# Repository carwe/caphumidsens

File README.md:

ARCHIVED on github -> migrated to codeberg: https://codeberg.org/carwe/caphumidsens

<b>code not usable due to never debugged bugs</b>

<b>code not usable due to never debugged bugs</b>

<b>code not usable due to never debugged bugs</b>

<b>code not usable due to never debugged bugs</b>

caphumidsens
============
Contains EAGLE-files for a pcb to convert soil moisture into frequency.

There are various revisions of the board:

classic design with NE555
-------------------------

###caphumidsens rev1
This was more or less a test, if the idea is working. It is quite big and unoptimized. Also the design of the capacitator is unnecessary complex.<br>
You need one NE555 (or CMOS-equivalent like TLC555) in SO-8, the other parts are of size 0805. C1=10nF; C2=100nF; R1=R2=120kOhm; D1=1N4148<br>
The chosen values let the output oscillate with around 74kHz, when dry and in air, down to around 4kHz, when the cap-part of the board is put into pure water, if you have chosen the TTL-555.

###caphumidsens rev2
...died an early death and was never physically fabricated.

###caphumidsens rev3
...is space-optimized and the components are nicely placed in a row, the draw-back is, they are too close - unfortuntely I had some of them fabricated, so it needed some fiddling to solder. <b>Do not use this layout.</b> In the discussion about this board some ideas came along: you probably want to measure the humidity in the middle of the soil, at least not directly on the surface, where it varies most. And there should be some kind of safety-margin, you don't want to change the capacitance by moving it slightly in and out of the soil. Next design should adress this.

###caphumidsens rev4
Here the capacitator was moved, so the humidity on the surface is no longer significant. Also the parts, which were too close to each other, got more space between them.

<pre>Measurements (frequency in kHz):
                Rev1/TTL        Rev1/CMOS        Rev3/CMOS        Rev4/CMOS
air              74,9              66,8            91,6              ?
dry soil         73,1              65,3            91,3              ?
half-wet soil    64,0              52,5            73,4              ?
wet soil         13,4              17,8            37,6              ?
water             3,4               ?               ?                ?</pre>

redesign with ATtiny
--------------------

###caphumidsens rev5
Lately I discussed about the project, and it quickly became clear, that it should be possible to connect output-pins of more than one caphumidsens-pcb over a single line with a master-controller. Using a bus has clear advantages (otherwise, you have to use a dedicated line to transport each signal, of course), so I designed a first draft.

With a ATtiny25/45/85 (maybe ATtiny13A too, if the code fits into it - comparator is existent there too, and the pinout is the same) I tried to create a NE555-similar structure. A capacitator is charged to a higher voltage, then discharged to a lower voltage, and a comparator toggles the (dis-)charging.

You have to decide if you want to use the internal voltage reference or not. If yes, you have to sense the voltage with AIN1 and compare it to the internal voltage reference and AIN0 as external voltage reference. If no, you have to sense the voltage with AIN0 and compare it witho two external voltage references on ADC0-ADC3. Some time ago I wrote here you could not compare against the internal reference and the multiplexer at the same time and save a pin - which is true, but you don't need to, it just requires another layout. To use the internal voltage reference for one side of the comparison, you have to have your sense pin as negative side on AIN1, and select the internal reference for the positive side of the AC. Then compare negative side AIN1 with AIN0 as the positive side of the AC. But, this is not what I designed.

I chose to use two external voltage references, created by division of VCC, same as in 555. This way it makes no difference what exact voltage VCC is, it can even change, the resulting frequency is independent. So you sense the voltage on AIN0 as positive side of the AC, and the multiplexer as negative side, and switch the input of the multiplexer as you charge (ADC1) and discharge (ADC2).

Pin 6 is set to VCC or GND to charge or discharge the capacitator, pin 5 senses the voltage and compares it to pin 3 or 7. On pin 1 (and maybe pin 2, if clock-ínput is not needed) you can talk a protocol you like - a simple frequency like the NE555 or something more complex, maybe pulling the line low against a central pull-resistor (I2C-like), sending your ID (stored in EEPROM) followed by the measured capacity. After you have written out a bit of your ID, you read it back, if another sensor is sending too (pulling the line dominates leaving the line alone, so the ID with the most "pulling bits" is the highest, CAN-like). The frequency of the messages is low enough, so that collisions should hardly occur, and if, you simply repeat your message.

Pin 1 is the reset/debugwire-pin too, so you can use debugwire to program the harder part of measuring the capacity, as you don't need the output-pin during this time. I have added small capacitators to even out the reference voltages, if that is necessary.

In the next days, I should receive some of them from the manufacturer.

Update five years later, 2017: yes I got them. and then I forgot them. And, I would not use Eagle anymore. Never again. Took me an hour to find an old version I could use with my licence, it brought me to tears what happened to this program after being bought by Autodesk. Everybody warned me to use this nonfree software, and I thought "whatever... works for me." - then reality hit.

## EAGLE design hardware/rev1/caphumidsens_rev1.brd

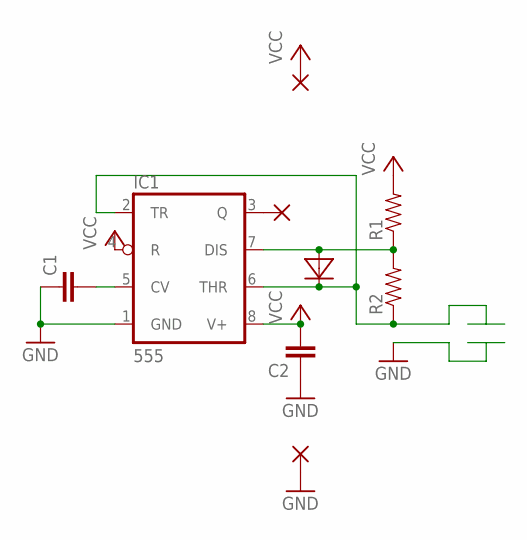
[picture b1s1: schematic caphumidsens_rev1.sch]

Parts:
C1, C2: CAP0805; 0805
D1: DIODE_0805
GND: WIREPADSMD2,54-5,08; SMD2,54-5,08
IC1: 555; SO08
OUT: WIREPADSMD2,54-5,08; SMD2,54-5,08
R1, R2: RESISTOR0805-RES; 0805
VCC: WIREPADSMD2,54-5,08; SMD2,54-5,08

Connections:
CAP+: D1.1 (C), IC1.2 (TR), IC1.6 (THR), R2.1
GND: C1.1, C2.1, GND.1, IC1.1 (GND)
unnamed: D1.2 (A), IC1.7 (DIS), R1.1, R2.2
unnamed: C1.2, IC1.5 (CV)
unnamed: IC1.3 (Q), OUT.1
VCC: C2.2, IC1.4 (R), IC1.8 (V+), R1.2, VCC.1

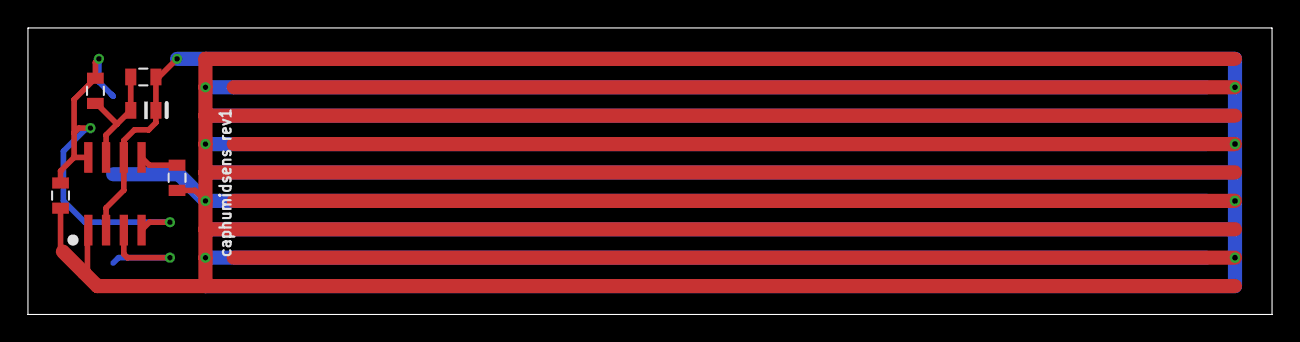
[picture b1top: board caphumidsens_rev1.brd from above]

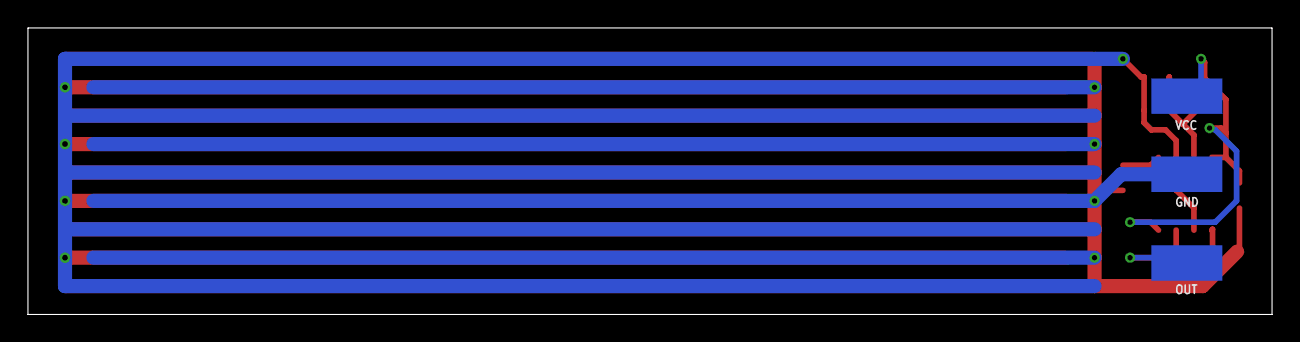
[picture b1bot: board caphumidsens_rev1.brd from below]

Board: 2 copper layers, 89.0 x 20.5 mm, 9 parts (3 on the bottom side), 6 nets.

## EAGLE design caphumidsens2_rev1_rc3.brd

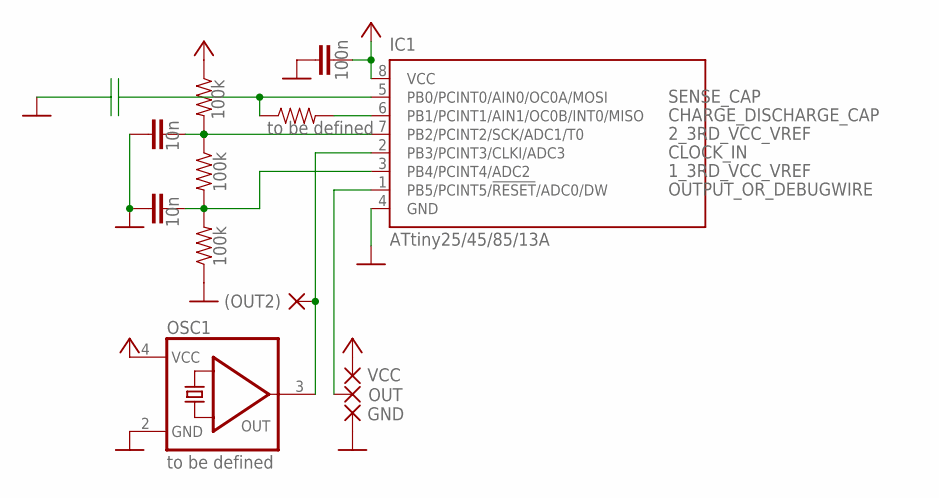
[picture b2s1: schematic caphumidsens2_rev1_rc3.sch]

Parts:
(OUT2): WIREPADSMD2,54-5,08; SMD1,27-2,54
C1: 100n; 0805
C2, C3: 10n; 0805
GND: WIREPADSMD2,54-5,08; SMD1,27-2,54
IC1: ATtiny25/45/85/13A; 8S1
OSC1: to be defined; XO32
OUT: WIREPADSMD2,54-5,08; SMD1,27-2,54
R1, R2, R3: 100k; 0805
R4: to be defined; 0805
VCC: WIREPADSMD2,54-5,08; SMD1,27-2,54

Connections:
1_3RD_VCC_VREF: C2.1, IC1.3 (PB4/PCINT4/ADC2), R2.2, R3.2
2_3RD_VCC_VREF: C3.2, IC1.7 (PB2/PCINT2/SCK/ADC1/T0), R1.2, R2.1
CHARGE_DISCHARGE_CAP: IC1.6 (PB1/PCINT1/AIN1/OC0B/INT0/MISO), R4.2
CLOCK_IN: (OUT2).1, IC1.2 (PB3/PCINT3/CLKI/ADC3), OSC1.3 (OUT)
GND: C1.1, C2.2, C3.1, GND.1, IC1.4 (GND), OSC1.2 (GND), R3.1
OUTPUT_OR_DEBUGWIRE: IC1.1 (PB5/PCINT5/!RESET!/ADC0/DW), OUT.1
SENSE_CAP: IC1.5 (PB0/PCINT0/AIN0/OC0A/MOSI), R4.1
VCC: C1.2, IC1.8 (VCC), OSC1.4 (VCC), R1.1, VCC.1

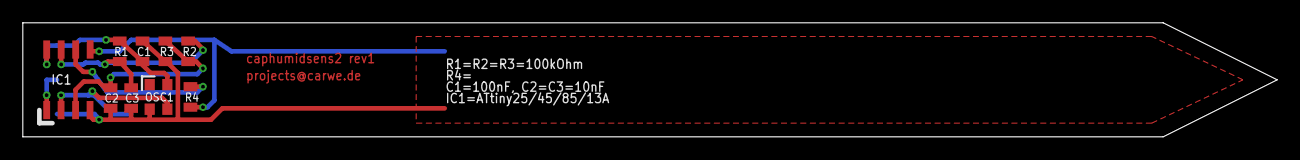
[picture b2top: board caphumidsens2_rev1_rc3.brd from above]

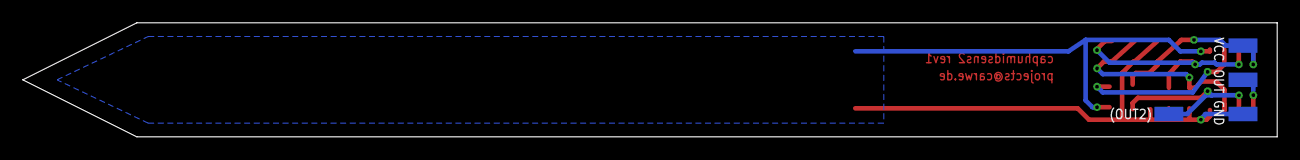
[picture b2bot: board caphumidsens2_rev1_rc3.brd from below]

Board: 2 copper layers, 110.0 x 10.0 mm, 13 parts (4 on the bottom side), 8 nets.

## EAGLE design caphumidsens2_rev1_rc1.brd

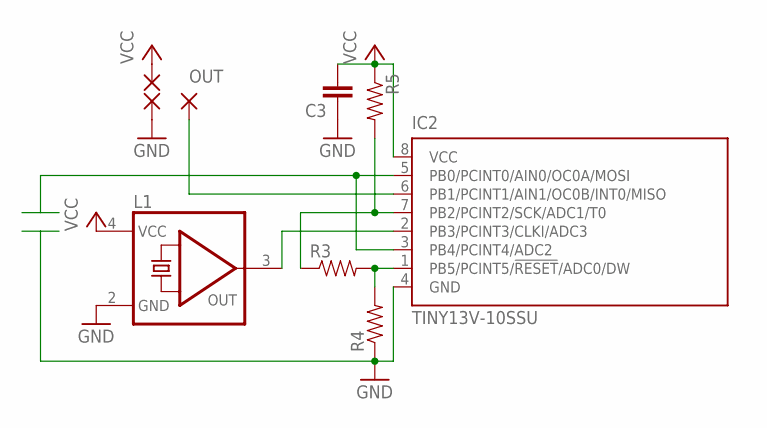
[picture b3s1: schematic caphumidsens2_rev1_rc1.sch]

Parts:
C3: CAP0805; 0805
GND: WIREPADSMD2,54-5,08; SMD1,27-2,54
IC2: TINY13V-10SSU; 8S1
L1: XO32-OSCILLATOR; XO32
OUT: WIREPADSMD2,54-5,08; SMD1,27-2,54
R3, R4, R5: RESISTOR0805-RES; 0805
VCC: WIREPADSMD2,54-5,08; SMD1,27-2,54

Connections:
1_3RD_VCC: IC2.1 (PB5/PCINT5/!RESET!/ADC0/DW), R3.2, R4.2
2_3RD_VCC: IC2.7 (PB2/PCINT2/SCK/ADC1/T0), R3.1, R5.2
CAP+: IC2.3 (PB4/PCINT4/ADC2), IC2.5 (PB0/PCINT0/AIN0/OC0A/MOSI)
GND: C3.1, GND.1, IC2.4 (GND), L1.2 (GND), R4.1
OSC: IC2.2 (PB3/PCINT3/CLKI/ADC3), L1.3 (OUT)
OUT: IC2.6 (PB1/PCINT1/AIN1/OC0B/INT0/MISO), OUT.1
VCC: C3.2, IC2.8 (VCC), L1.4 (VCC), R5.1, VCC.1

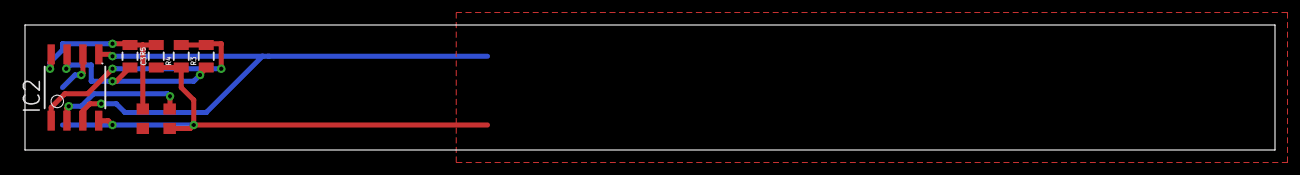
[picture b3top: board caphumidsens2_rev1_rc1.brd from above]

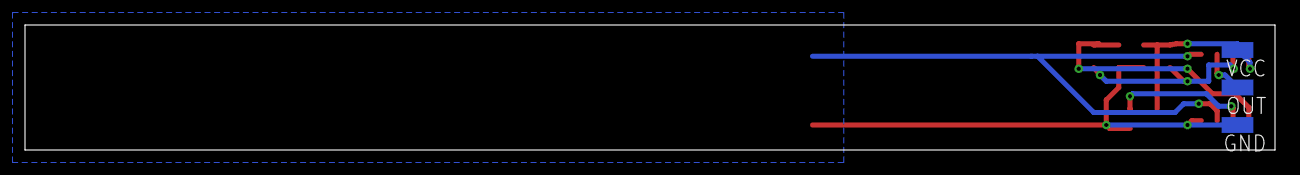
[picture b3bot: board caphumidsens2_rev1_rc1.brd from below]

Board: 2 copper layers, 100.0 x 10.0 mm, 9 parts (3 on the bottom side), 7 nets.

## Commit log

2012-09-15 added the eagle-files
2012-11-05 added rev3-files
2012-11-05 fiddling with the readme
2012-11-06 added rev2-files
2012-11-11 added files for rev4 rc1
2012-11-12 added files for rev4 rc2
2012-11-12 corrected mistake in readme
2012-11-12 added measurements for rev1&rev3
2012-11-12 changed from tabs to spaces
2012-11-12 moved vias closer to their signal's pad's
2012-11-12 moved text to honor border saveguards
2012-11-16 preparing rev4-final
2012-11-16 renamed last layout into final rev4
2012-12-07 added rule-file for OSHpark
2012-12-07 added files for a new version, not longer with 555 timer, but atmel-microcontroller
2012-12-07 misc
2012-12-10 hopefully corrected the readme
2012-12-10 added redesigned rc3 and updated readme
2012-12-11 readme misc
2012-12-11 rc3 finetuned
2012-12-11 finetuning, misc
2012-12-12 removed tPlace-Layer from ATtiny
2012-12-12 removed tPlace-Layer from 0805-packages
2012-12-13 moved via to a better place
2012-12-13 solder mask misc
2012-12-13 'improved' routing
2012-12-13 tName misc
2012-12-13 added 2nd output-pad, if osc1 isn't needed
2012-12-24 misc; renamed 2_rev1_rc3 into _rev5
2012-12-24 renamed dru-file back to original name
2012-12-24 reworked silkscreen
2012-12-24 silkscreen misc
2012-12-30 switched to v6-fileformat
2012-12-30 unified layer-colors
2012-12-30 unified active layers
2012-12-30 moved files into separate directories
2013-01-01 readme updated
2017-06-28 first commit of attiny85 code
2017-06-28 add datasheets tiny13a/25/45/85
2017-06-28 move board layouts to subdir
2017-06-29 create build script
2017-06-30 bugfix: enable global interrupts
2017-06-30 add built firmware as example
2017-06-30 add disassemble cap. to buildscript
2017-07-05 replace BIT_CLEAR/BIT_SET with BIT_BOOL_SET
2017-07-07 fixed logic of analog comparator, still not working as expected
2017-07-07 disable digital input hardware of analog inputs
2017-07-08 forgot firmware
2018-03-01 pushing latest... err... wuerg-in-progress-code to repo
